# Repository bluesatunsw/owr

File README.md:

# owr
This repo includes all software necessary to operate the Test Rover Platform
that is being designed and developed in the OWR project.
=======

## System Setup
A guide is available on the
[owr-docs](https://github.com/bluesatunsw/owr-docs/tree/main/src/guides/container_setup.md)
repository.

## Useful Command index
| Command                                                               | Effect                                                                                          |
| -------------------------------                                       | --------------------------------                                                                |
| `podman compose -f "$PWD/.devcontainer/docker-compose.yml" up -d`     | Run in the git root to build/restart/start the Docker container.                                |
| `podman compose -f "$PWD/.devcontainer/docker-compose-obc.yml" up -d` | Run in the git root to build/restart/start the Docker container **with obc specific settings!** |
| `podman exec -it --latest /bin/bash`                                  | Enter the docker container after launching it with the devcontainer.                            |
| `./utils/init.bash`                                                   | Run after `cd`'ing into `/workspaces/owr` in the container to source the ROS env and tools      |
| `colcon build --symlink-install`                                      | Runs the `colcon` meta build system, builds ALL rover packages!                                 |
| `ros2 launch rover rover.launch.py`                                   | Launch the robot state publisher. Just leave this running.                                      |
| `rqt`                                                                 | The flexible ROS2 viewer, useful for debugging topic flows and looking at raw topics.           |
| `rviz2`                                                               | Useful for visualizing TF2 / LiDAR / etc... data to see if it looks okay.                       |
| `podman rm --force --latest -t 0`                                     | Kill the podman container with the latest creation date (quickly)                               |

NOTE: `podman compose` will take a VERY long time! on uni Wi-Fi \~5min due to
the amount of packages it installs (\~5GB). There is also [a podman
bug](github.com/containers/podman/issues/16541) that invokes a postprocessing
step on the overlay filesystem, this will take **upwards of 10 minutes!** 

NOTE: `./utils/init.bash` will source the appropriate files as well as put you
in a 10-deep nested shell - running an invalid command will kill 1 level!

### Less Common Commands

| Command                                                               | Effect                                                                                    |
| -------------------------------                                       | --------------------------------                                                          |
| `ros2 launch rover rsp.launch.py`                                     | Robot State Publisher, publishes the URDF+JSP, to make it viewable in Lichtblick / Rviz2. |
| `xacro ./src/rover/description/robot.urdf.xacro > ./build/rover.urdf` | Compiles the xacro into a singular urdf file                                              |
| `ros2 run key_teleop key_teleop --ros-args -p twist_stamped_enabled:=True -r /key_vel:=/diff_drive_base_controller/cmd_vel` | Record keyboard imputs and publish them as Twist2d values, which ROS2Control is listening for!

### Useful Podman Commands
| Command                                                               | Effect                                                                                    |
| -------------------------------                                       | ---------------------------------                                                         |
| `podman images`                                                       | Lists current podman images                                                               |
| `podman rmi {ID} --force`                                             | Remove relevant image. Replace the ID with output from the above command                  |

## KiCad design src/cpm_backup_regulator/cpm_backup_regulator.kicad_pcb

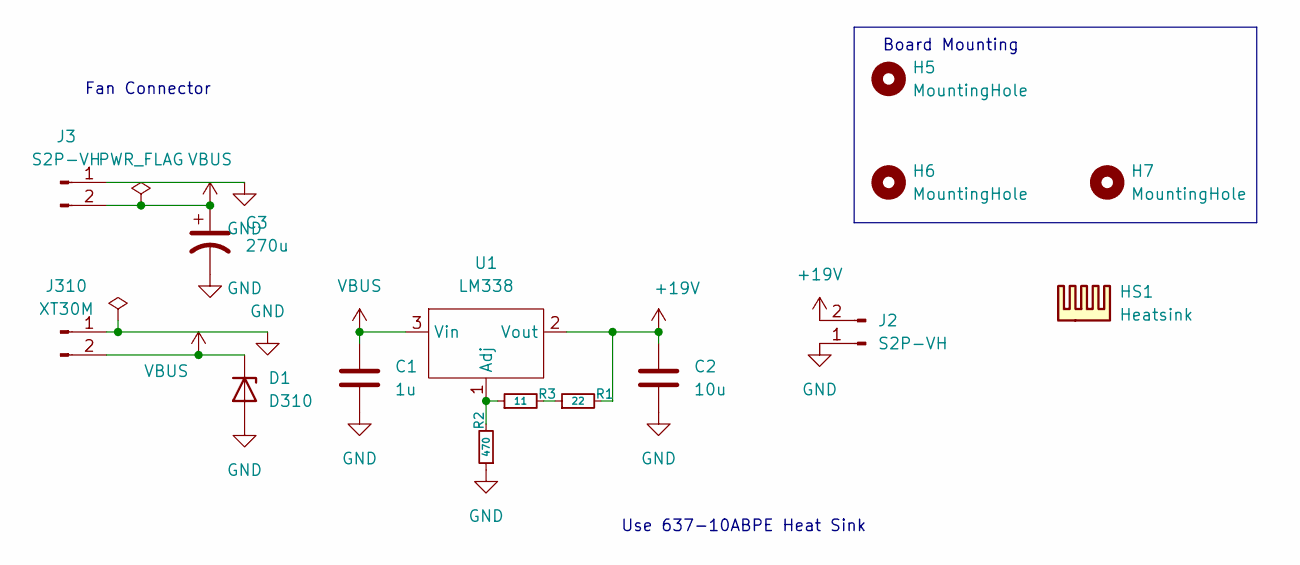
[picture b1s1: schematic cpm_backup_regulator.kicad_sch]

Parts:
C1: 1u; C_0805_2012Metric
C2: 10u; C_1210_3225Metric
C3: 270u; CP_Elec_10x10
D1: D310; D_SMF
H5, H6, H7: MountingHole; M2.5_Internal
HS1: Heatsink; Heatsink_Fischer_SK129-STS_42x25mm_2xDrill2.5mm
J2: S2P-VH; B2P-VH
J3: S2P-VH; BM02B-PASS
J310: XT30M; AMASS_XT30PW-M_1x02_P2.50mm_Horizontal
R1: 22; C_0402_1005Metric
R2: 470; C_0402_1005Metric
R3: 11; C_0402_1005Metric
U1: LM338; TO-220F-3_Vertical

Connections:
+19V: C2.1, J2.2, R1.2, U1.2 (Vout)
GND: C1.2, C2.2, C3.2, D1.2 (A), J2.1, J3.1, J310.1, R2.1
unnamed: R1.1, R3.2
unnamed: R2.2, R3.1, U1.1 (Adj)
VBUS: C1.1, C3.1, D1.1 (K), J3.2, J310.2, U1.3 (Vin)

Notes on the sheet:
Fan Connector
Board Mounting
Use 637-10ABPE Heat Sink

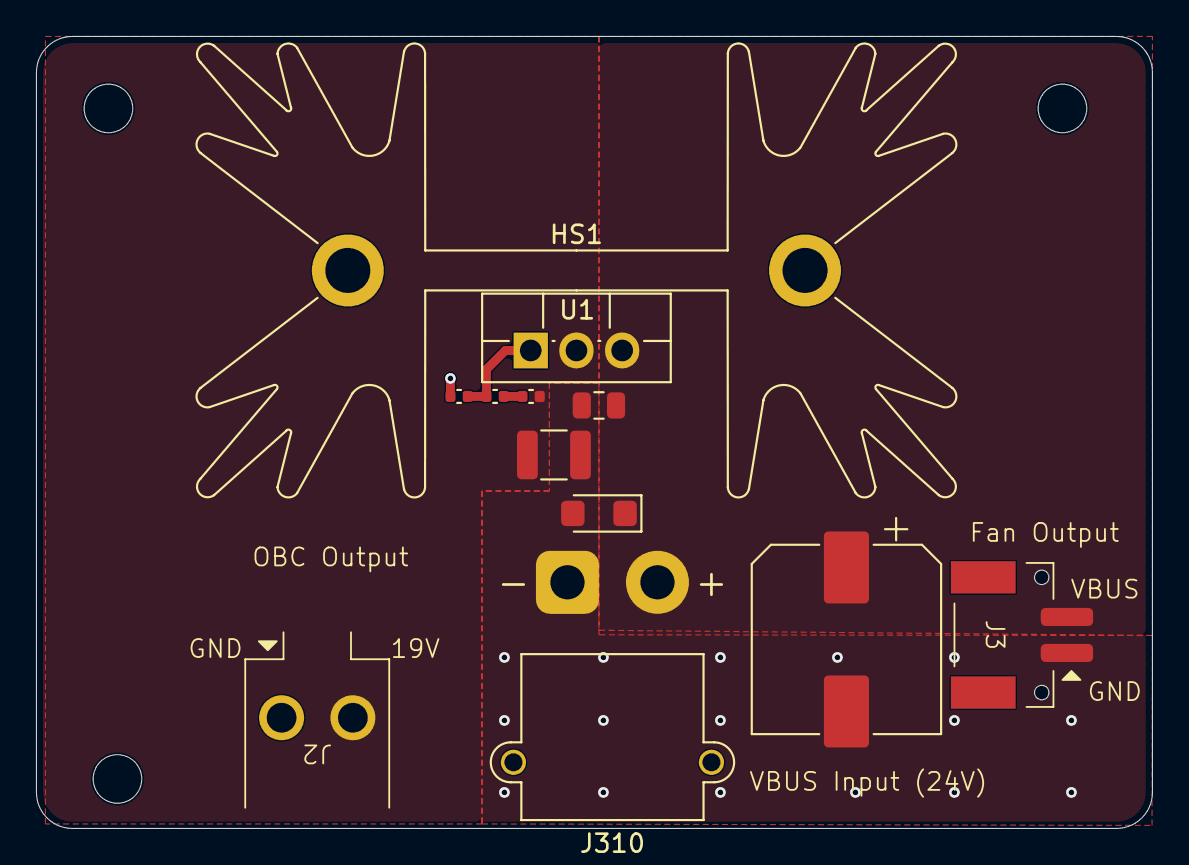
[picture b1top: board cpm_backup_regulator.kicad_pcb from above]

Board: 2 copper layers, 62.0 x 44.0 mm, 15 parts (0 on the bottom side), 5 nets.

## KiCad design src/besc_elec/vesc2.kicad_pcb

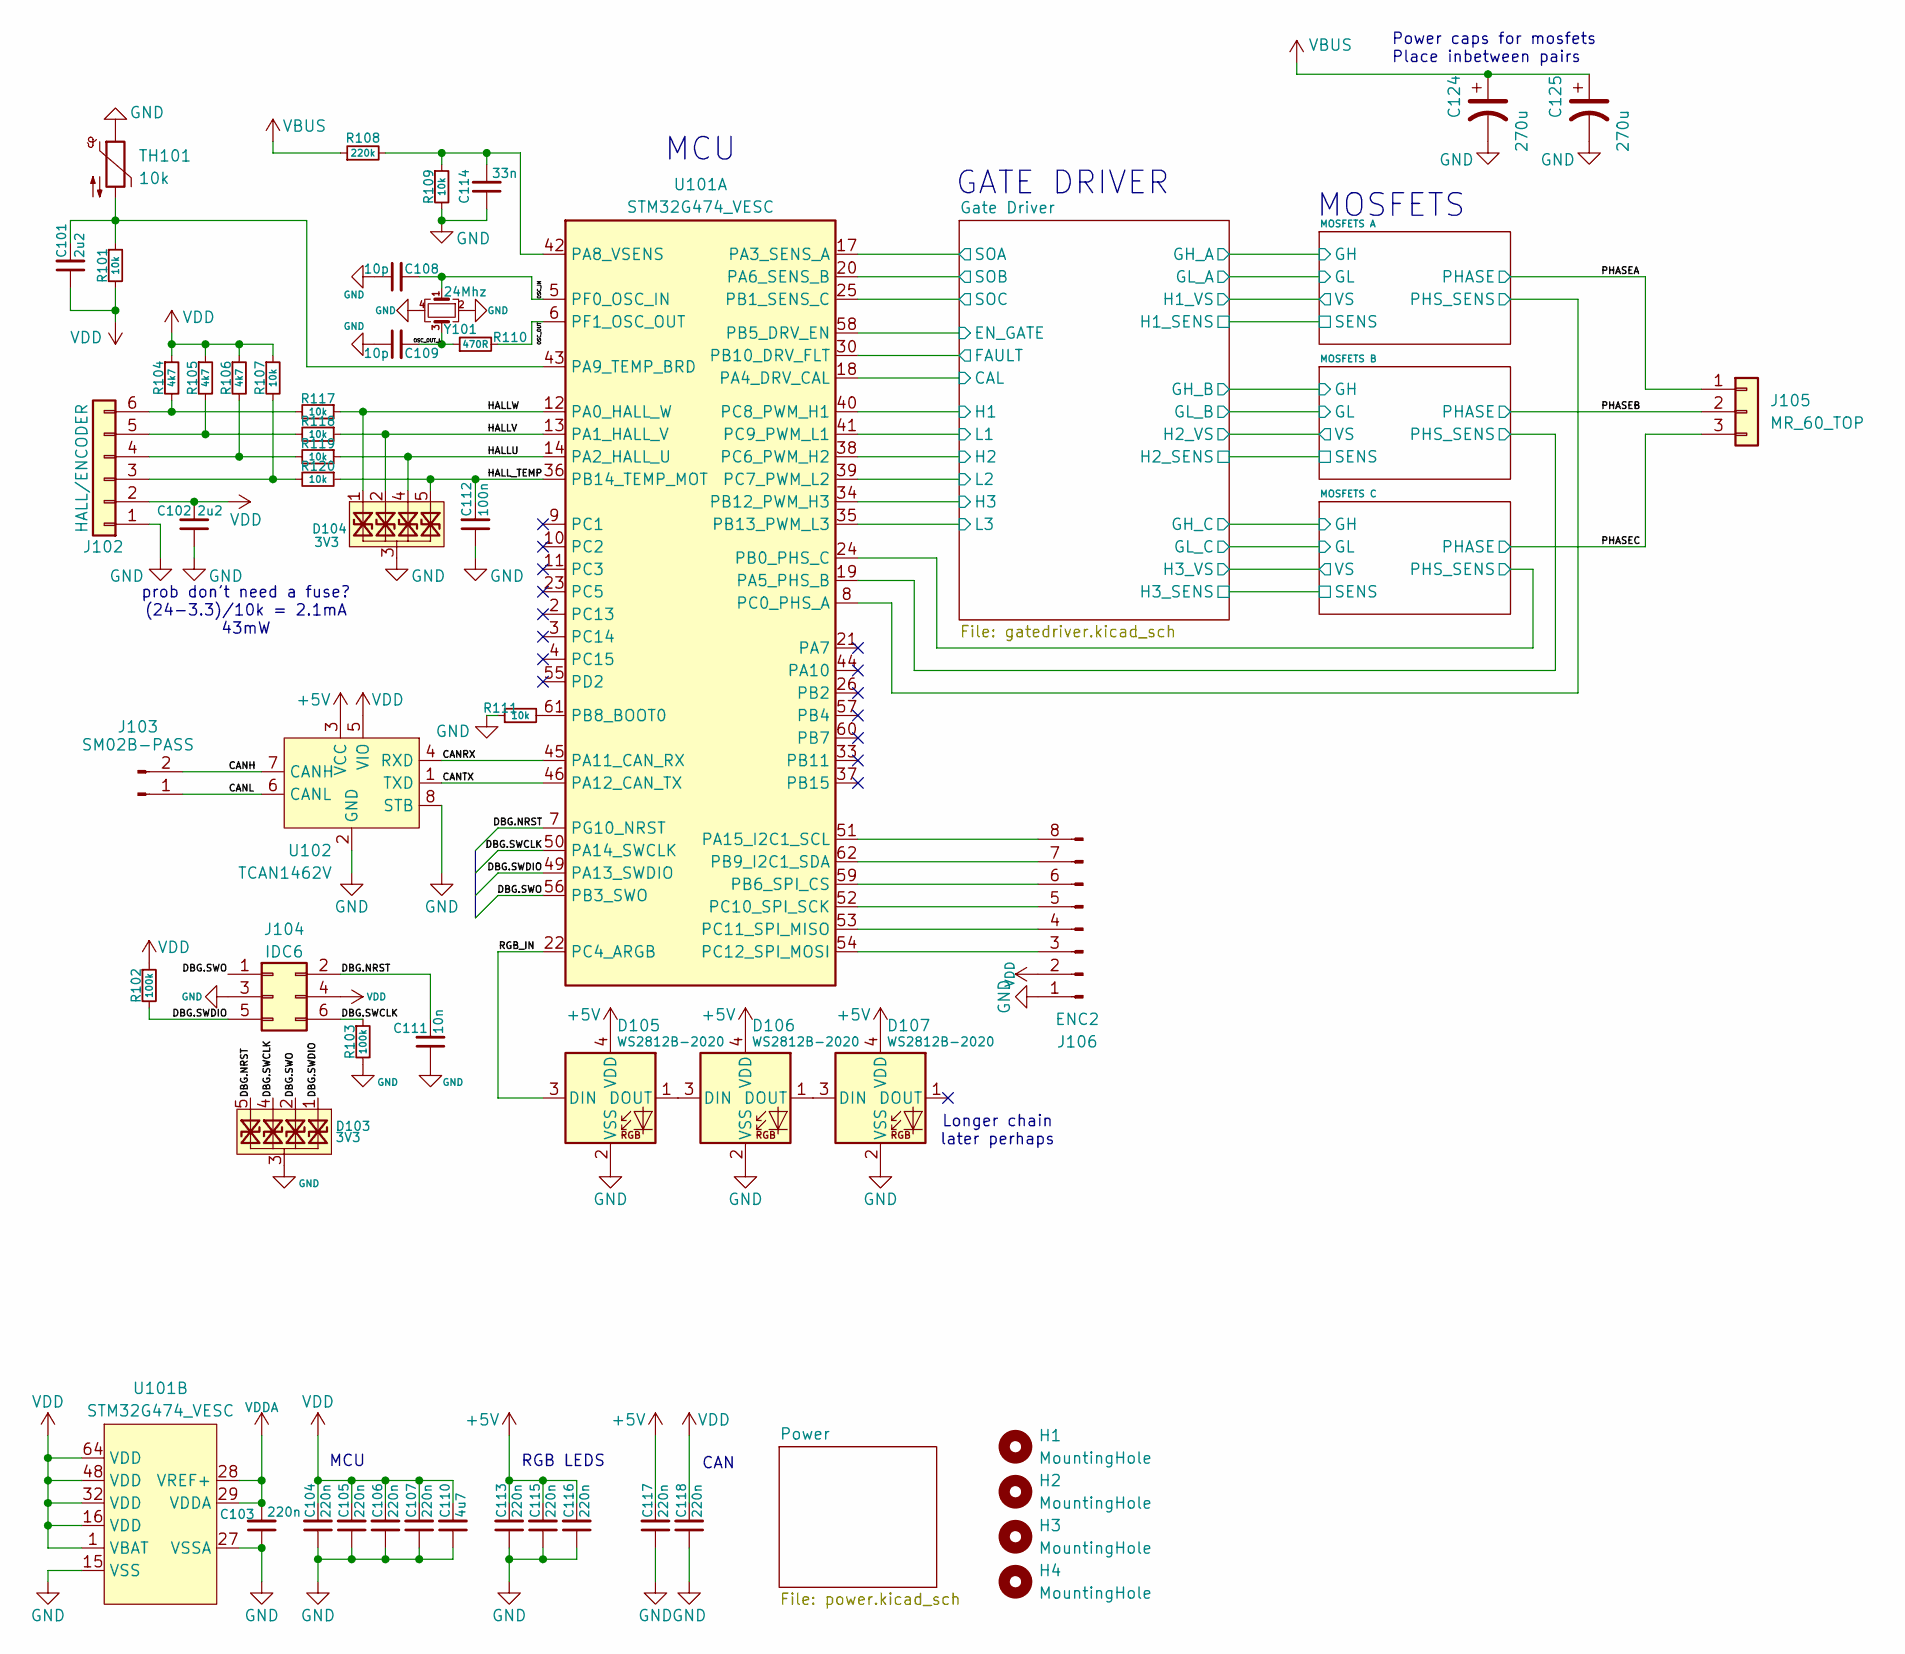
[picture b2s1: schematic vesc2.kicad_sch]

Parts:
C101, C102: 2u2; C_0603_1608Metric
C103, C104, C105, C106, C107, C113, C115, C116, C117, C118: 220n; C_0402_1005Metric
C108, C109: 10p; C_0402_1005Metric
C110: 4u7; C_0805_2012Metric
C111: 10n; C_0402_1005Metric
C112: 100n; C_0402_1005Metric
C114: 33n; C_0402_1005Metric
C124, C125: 270u; CP_Elec_10x10
D103, D104: 3V3; Diodes_UDFN-10_1x2.5mm_P0.5mm
D105, D106, D107: WS2812B-2020
H1, H2, H3, H4: MountingHole; M2.5_Edge
J102: HALL/ENCODER; BM06B-PASS
J103: SM02B-PASS; BM02B-PASS
J104: IDC6
J105: MR_60_TOP; MR60-F-TopMount
J106: ENC2; JST_PH_B8B-PH-SM4-TB_1x08-1MP_P2.00mm_Vertical
R101, R107, R109, R111, R117, R118, R119, R120: 10k; R_0402_1005Metric
R102, R103: 100k; R_0402_1005Metric
R104, R105, R106: 4k7; R_0402_1005Metric
R108: 220k; R_0402_1005Metric
R110: 470R; R_0402_1005Metric
TH101: 10k; R_0402_1005Metric
U101: STM32G474_VESC; LQFP-64-0.5
U102: TCAN1462V; SOIC-8_3.9x4.9mm_P1.27mm
Y101: 24Mhz; Crystal_SMD_2016-4Pin_2.0x1.6mm

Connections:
+5V: C113.2, C115.2, C116.2, C117.2, D105.4 (VDD), D106.4 (VDD), D107.4 (VDD), U102.3 (VCC); also elsewhere on the board
/CANH: J103.2, U102.7 (CANH)
/CANL: J103.1, U102.6 (CANL)
/CANRX: U101.45 (PA11_CAN_RX), U102.4 (RXD)
/CANTX: U101.46 (PA12_CAN_TX), U102.1 (TXD)
/DBG.NRST: C111.2, D103.5, D103.6, J104.2, U101.7 (PG10_NRST)
/DBG.SWCLK: D103.4, D103.7, J104.6, R103.1, U101.50 (PA14_SWCLK)
/DBG.SWDIO: D103.1, D103.10, J104.5, R102.2, U101.49 (PA13_SWDIO)
/DBG.SWO: D103.2, D103.9, J104.1, U101.56 (PB3_SWO)
/Gate Driver/CAL: U101.18 (PA4_DRV_CAL); also elsewhere on the board
/Gate Driver/EN_GATE: U101.58 (PB5_DRV_EN); also elsewhere on the board
/Gate Driver/FAULT: U101.30 (PB10_DRV_FLT); also elsewhere on the board
/Gate Driver/H1: U101.40 (PC8_PWM_H1); also elsewhere on the board
/Gate Driver/H2: U101.38 (PC6_PWM_H2); also elsewhere on the board
/Gate Driver/H3: U101.34 (PB12_PWM_H3); also elsewhere on the board
/Gate Driver/L1: U101.41 (PC9_PWM_L1); also elsewhere on the board
/Gate Driver/L2: U101.39 (PC7_PWM_L2); also elsewhere on the board
/Gate Driver/L3: U101.35 (PB13_PWM_L3); also elsewhere on the board
/Gate Driver/SOA: U101.17 (PA3_SENS_A); also elsewhere on the board
/Gate Driver/SOB: U101.20 (PA6_SENS_B); also elsewhere on the board
/Gate Driver/SOC: U101.25 (PB1_SENS_C); also elsewhere on the board
/HALLU: D104.4, D104.7, R119.1, U101.14 (PA2_HALL_U)
/HALLV: D104.2, D104.9, R118.1, U101.13 (PA1_HALL_V)
/HALLW: D104.1, D104.10, R117.1, U101.12 (PA0_HALL_W)
/HALL_TEMP: C112.2, D104.5, D104.6, R120.1, U101.36 (PB14_TEMP_MOT)
/MOSFETS A/PHS_SENS: U101.8 (PC0_PHS_A); also elsewhere on the board
/MOSFETS B/PHS_SENS: U101.19 (PA5_PHS_B); also elsewhere on the board
/MOSFETS C/PHS_SENS: U101.24 (PB0_PHS_C); also elsewhere on the board
/OSC_IN: C108.2, U101.5 (PF0_OSC_IN), Y101.1
/OSC_OUT: R110.2, U101.6 (PF1_OSC_OUT)
/OSC_OUT_L: C109.2, R110.1, Y101.3
/PHASEA: J105.1; also elsewhere on the board
/PHASEB: J105.2; also elsewhere on the board
/PHASEC: J105.3; also elsewhere on the board
/RGB_IN: D105.3 (DIN), U101.22 (PC4_ARGB)
GND: C102.1, C103.1, C104.1, C105.1, C106.1, C107.1, C108.1, C109.1, C110.1, C111.1, C112.1, C113.1, C114.1, C115.1, C116.1, C117.1, C118.1, C124.2, C125.2, D103.3, D103.8, D104.3, D104.8, D105.2 (VSS), D106.2 (VSS), D107.2 (VSS), J102.1, J104.3, J106.1, R103.2, R109.2, R111.1, TH101.1, U101.15 (VSS), U101.27 (VSSA), U101.31 (VSS), U101.47 (VSS), U101.63 (VSS), U102.2 (GND), U102.8 (STB), Y101.2, Y101.4; also elsewhere on the board
unnamed: D105.1 (DOUT), D106.3 (DIN)
unnamed: D106.1 (DOUT), D107.3 (DIN)
unnamed: J102.3, R107.2, R120.2
unnamed: J102.4, R106.2, R119.2
unnamed: J102.5, R105.2, R118.2
unnamed: J102.6, R104.2, R117.2
unnamed: J106.3, U101.54 (PC12_SPI_MOSI)
unnamed: J106.4, U101.53 (PC11_SPI_MISO)
unnamed: J106.5, U101.52 (PC10_SPI_SCK)
unnamed: J106.6, U101.59 (PB6_SPI_CS)
unnamed: J106.7, U101.62 (PB9_I2C1_SDA)
unnamed: J106.8, U101.51 (PA15_I2C1_SCL)
unnamed: C114.2, R108.2, R109.1, U101.42 (PA8_VSENS)
unnamed: C101.2, R101.1, TH101.2, U101.43 (PA9_TEMP_BRD)
unnamed: R111.2, U101.61 (PB8_BOOT0)
VBUS: C124.1, C125.1, R108.1; also elsewhere on the board
VDD: C101.1, C102.2, C104.2, C105.2, C106.2, C107.2, C110.2, C118.2, J102.2, J104.4, J106.2, R101.2, R102.1, R104.1, R105.1, R106.1, R107.1, U101.1 (VBAT), U101.16 (VDD), U101.32 (VDD), U101.48 (VDD), U101.64 (VDD), U102.5 (VIO); also elsewhere on the board
VDDA: C103.2, U101.28 (VREF+), U101.29 (VDDA); also elsewhere on the board

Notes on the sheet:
RGB LEDS
Power caps for mosfets Place inbetween pairs
GATE DRIVER
MCU
CAN
MOSFETS
prob don't need a fuse? (24-3.3)/10k = 2.1mA 43mW
Longer chain later perhaps

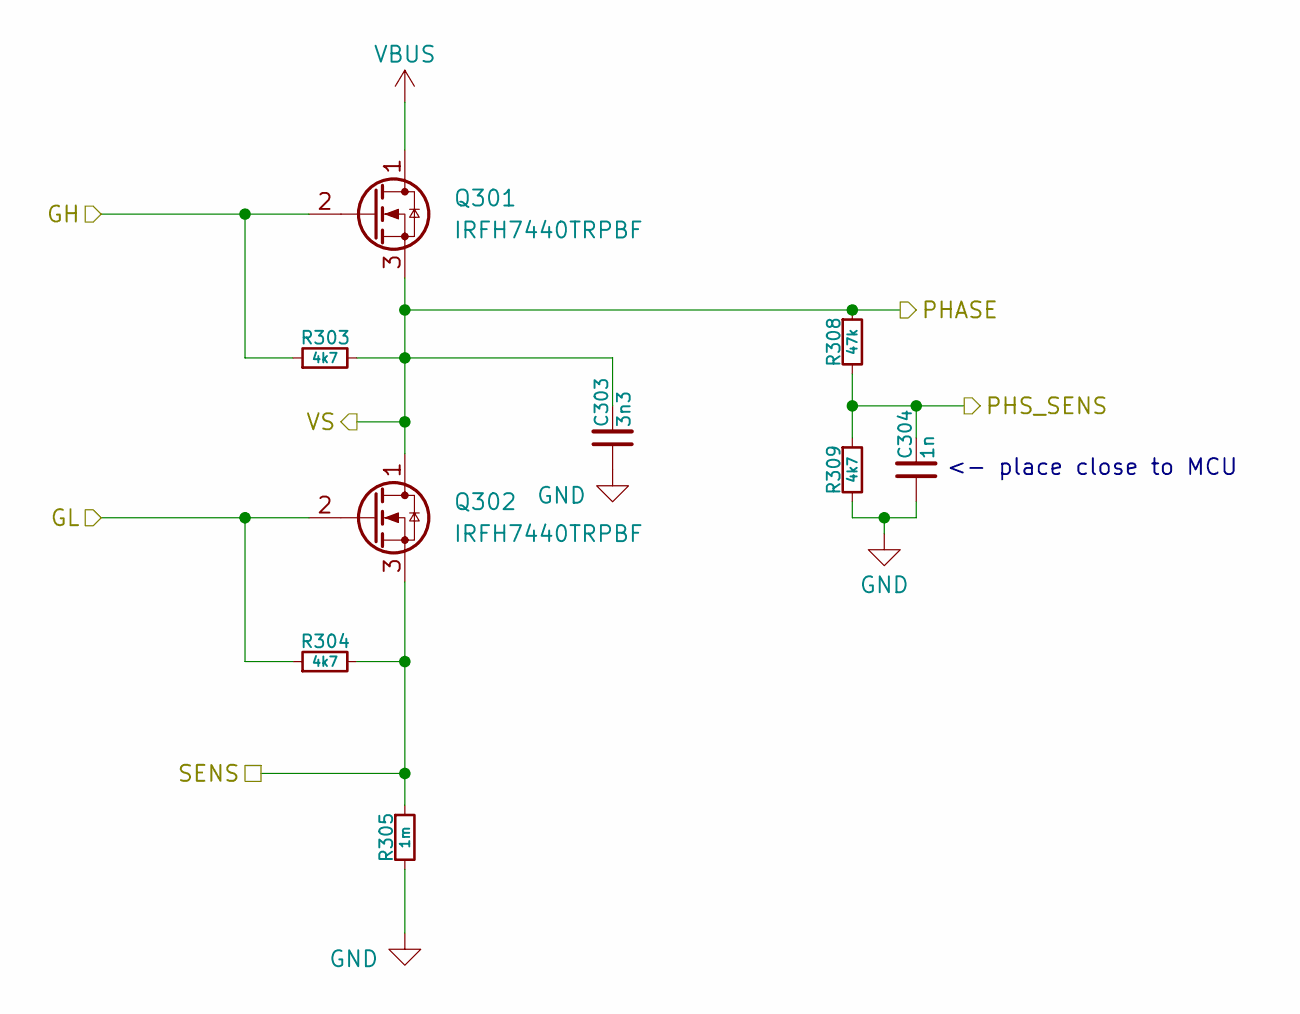
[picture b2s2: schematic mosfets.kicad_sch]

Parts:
C303: 3n3; C_0402_1005Metric
C304: 1n; C_0402_1005Metric
Q301, Q302: IRFH7440TRPBF; PQFN_5x6mm_E_DGS
R303, R304, R309: 4k7; R_0402_1005Metric
R305: 1m; R_2512_6332Metric
R308: 47k; R_0402_1005Metric

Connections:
/Gate Driver/GH_A: Q301.2 (G), R303.1; also elsewhere on the board
/Gate Driver/GL_A: Q302.2 (G), R304.1; also elsewhere on the board
/Gate Driver/H1_SENS: Q302.3 (S), R304.2, R305.1; also elsewhere on the board
/MOSFETS A/PHS_SENS: C304.2, R308.2, R309.1; also elsewhere on the board
/PHASEA: C303.2, Q301.3 (S), Q302.1 (D), R303.2, R308.1; also elsewhere on the board
GND: C303.1, C304.1, R305.2, R309.2; also elsewhere on the board
VBUS: Q301.1 (D); also elsewhere on the board

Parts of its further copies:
C403, C503: 3n3; C_0402_1005Metric
C404, C504: 1n; C_0402_1005Metric
Q401, Q402, Q501, Q502: IRFH7440TRPBF; PQFN_5x6mm_E_DGS
R403, R404, R408, R503, R504, R508: 4k7; R_0402_1005Metric
R405, R505: 1m; R_2512_6332Metric
R409, R509: 47k; R_0402_1005Metric

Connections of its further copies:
/Gate Driver/GH_B: Q401.2 (G), R403.1; also elsewhere on the board
/Gate Driver/GH_C: Q501.2 (G), R503.1; also elsewhere on the board
/Gate Driver/GL_B: Q402.2 (G), R404.1; also elsewhere on the board
/Gate Driver/GL_C: Q502.2 (G), R504.1; also elsewhere on the board
/Gate Driver/H2_SENS: Q402.3 (S), R404.2, R405.1; also elsewhere on the board
/Gate Driver/H3_SENS: Q502.3 (S), R504.2, R505.1; also elsewhere on the board
/MOSFETS B/PHS_SENS: C404.2, R408.1, R409.2; also elsewhere on the board
/MOSFETS C/PHS_SENS: C504.2, R508.1, R509.2; also elsewhere on the board
/PHASEB: C403.2, Q401.3 (S), Q402.1 (D), R403.2, R409.1; also elsewhere on the board
/PHASEC: C503.2, Q501.3 (S), Q502.1 (D), R503.2, R509.1; also elsewhere on the board
GND: C403.1, C404.1, C503.1, C504.1, R405.2, R408.2, R505.2, R508.2; also elsewhere on the board
VBUS: Q401.1 (D), Q501.1 (D); also elsewhere on the board

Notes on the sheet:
<- place close to MCU

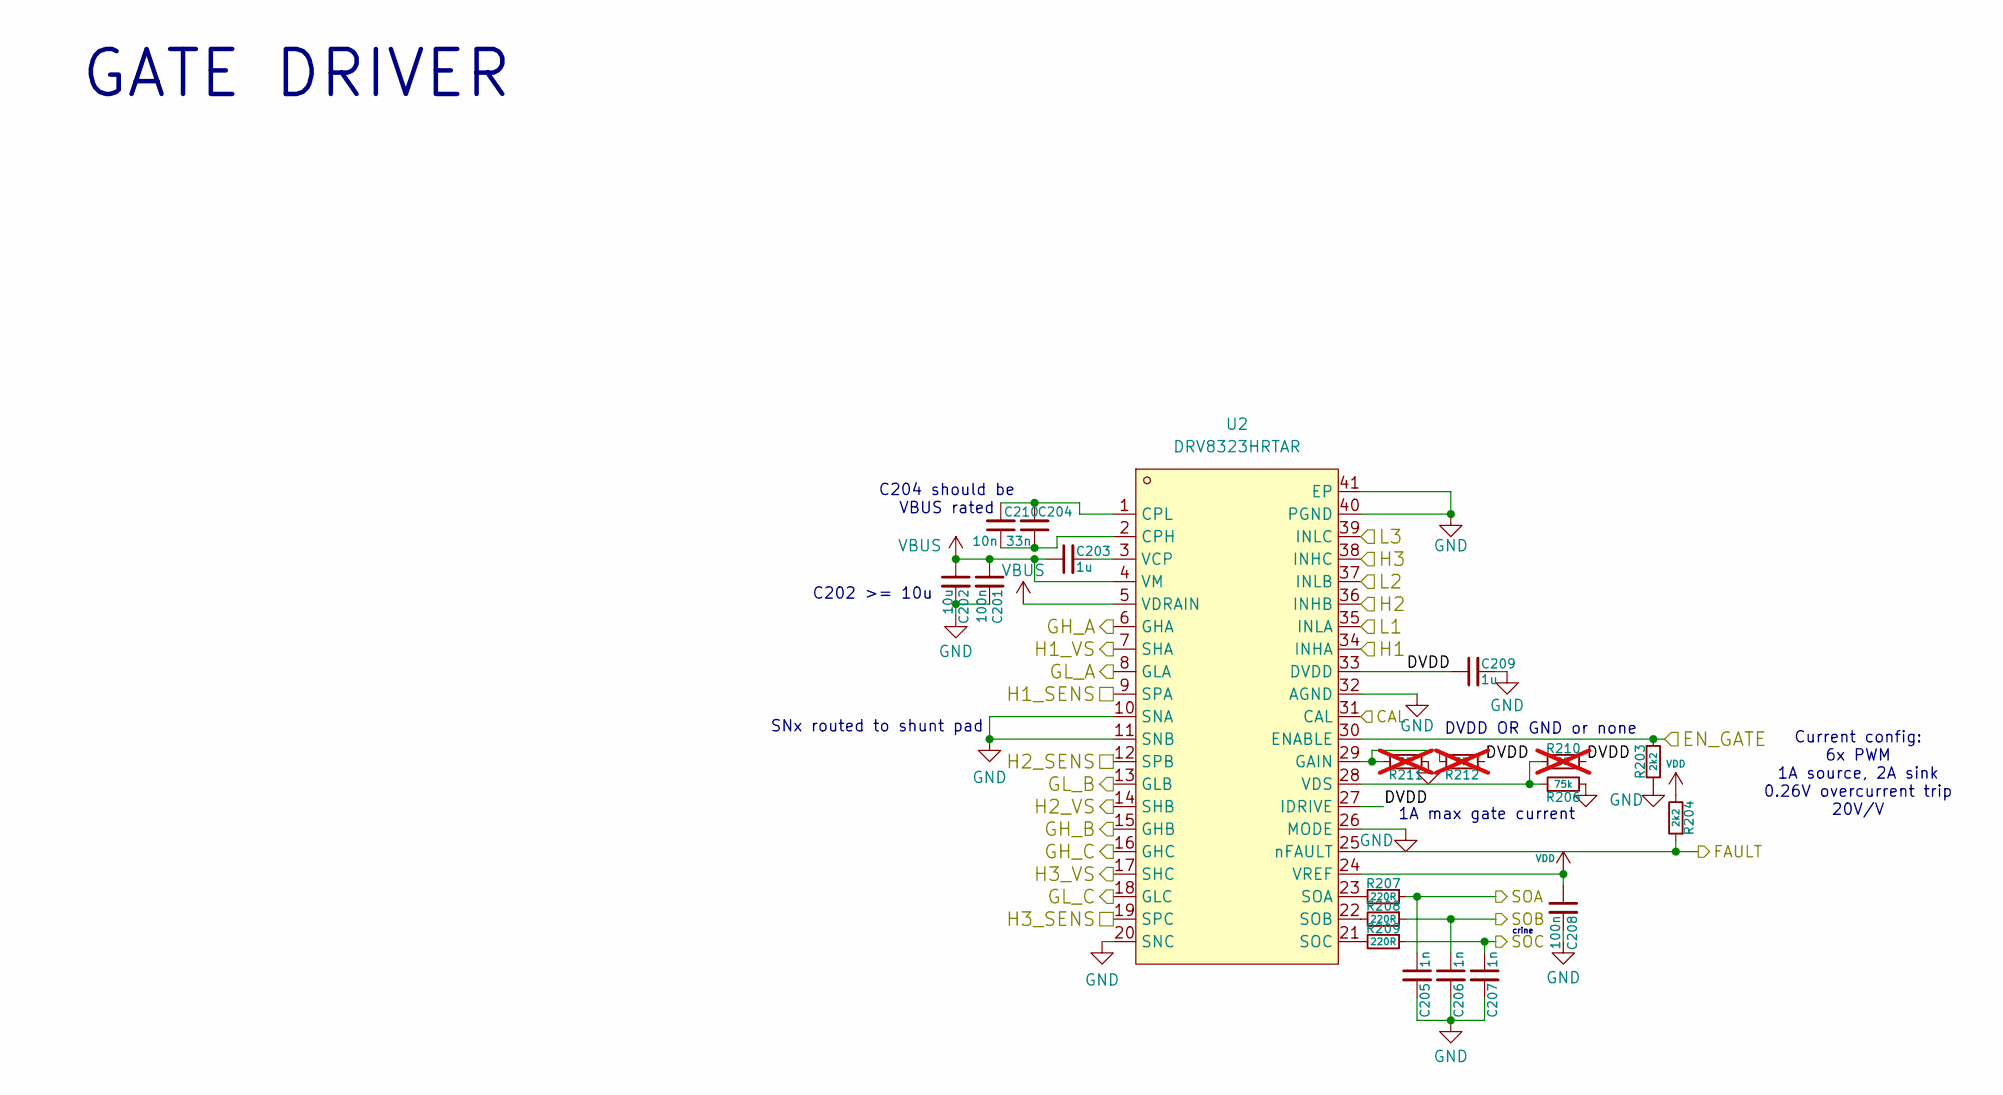
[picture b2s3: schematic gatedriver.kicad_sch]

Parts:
C201: 100n; C_0603_1608Metric
C202: 10u; C_1210_3225Metric
C203: 1u; C_0805_2012Metric
C204: 33n; C_0603_1608Metric
C205, C206, C207: 1n; C_0402_1005Metric
C208: 100n; C_0402_1005Metric
C209: 1u; C_0603_1608Metric
C210: 10n; C_0603_1608Metric
R203, R204: 2k2; R_0402_1005Metric
R206: 75k; R_0402_1005Metric
R207, R208, R209: 220R; R_0402_1005Metric
R210, R211, R212: 0R; R_0402_1005Metric; not fitted
U2: DRV8323HRTAR; QFN-40_L6.0-W6.0-P0.50-BL-EP4.5; MPN DRV8323HRTAR; LCSC Part C701783

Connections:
/Gate Driver/CAL: U2.31 (CAL); also elsewhere on the board
/Gate Driver/DVDD: C209.1, R210.1, R212.2, U2.27 (IDRIVE), U2.33 (DVDD)
/Gate Driver/EN_GATE: R203.1, U2.30 (ENABLE); also elsewhere on the board
/Gate Driver/FAULT: R204.1, U2.25 (nFAULT); also elsewhere on the board
/Gate Driver/GH_A: U2.6 (GHA); also elsewhere on the board
/Gate Driver/GH_B: U2.15 (GHB); also elsewhere on the board
/Gate Driver/GH_C: U2.16 (GHC); also elsewhere on the board
/Gate Driver/GL_A: U2.8 (GLA); also elsewhere on the board
/Gate Driver/GL_B: U2.13 (GLB); also elsewhere on the board
/Gate Driver/GL_C: U2.18 (GLC); also elsewhere on the board
/Gate Driver/H1: U2.34 (INHA); also elsewhere on the board
/Gate Driver/H1_SENS: U2.9 (SPA); also elsewhere on the board
/Gate Driver/H2: U2.36 (INHB); also elsewhere on the board
/Gate Driver/H2_SENS: U2.12 (SPB); also elsewhere on the board
/Gate Driver/H3: U2.38 (INHC); also elsewhere on the board
/Gate Driver/H3_SENS: U2.19 (SPC); also elsewhere on the board
/Gate Driver/L1: U2.35 (INLA); also elsewhere on the board
/Gate Driver/L2: U2.37 (INLB); also elsewhere on the board
/Gate Driver/L3: U2.39 (INLC); also elsewhere on the board
/Gate Driver/SOA: C205.1, R207.1; also elsewhere on the board
/Gate Driver/SOB: C206.1, R208.1; also elsewhere on the board
/Gate Driver/SOC: C207.1, R209.1; also elsewhere on the board
/PHASEA: U2.7 (SHA); also elsewhere on the board
/PHASEB: U2.14 (SHB); also elsewhere on the board
/PHASEC: U2.17 (SHC); also elsewhere on the board
GND: C201.2, C202.2, C205.2, C206.2, C207.2, C208.2, C209.2, R203.2, R206.2, R211.2, U2.10 (SNA), U2.11 (SNB), U2.20 (SNC), U2.26 (MODE), U2.32 (AGND), U2.40 (PGND), U2.41 (EP); also elsewhere on the board
unnamed: C204.1, C210.1, U2.2 (CPH)
unnamed: C204.2, C210.2, U2.1 (CPL)
unnamed: R211.1, R212.1, U2.29 (GAIN)
unnamed: R207.2, U2.23 (SOA)
unnamed: R208.2, U2.22 (SOB)
unnamed: R209.2, U2.21 (SOC)
unnamed: C203.2, U2.3 (VCP)
unnamed: R206.1, R210.2, U2.28 (VDS)
VBUS: C201.1, C202.1, C203.1, U2.4 (VM), U2.5 (VDRAIN); also elsewhere on the board
VDD: C208.1, R204.2, U2.24 (VREF); also elsewhere on the board

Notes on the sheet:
C204 should be VBUS rated
GATE DRIVER
Current config: 6x PWM 1A source, 2A sink 0.26V overcurrent trip 20V/V
DVDD OR GND or none
SNx routed to shunt pad
C202 >= 10u
crine
1A max gate current

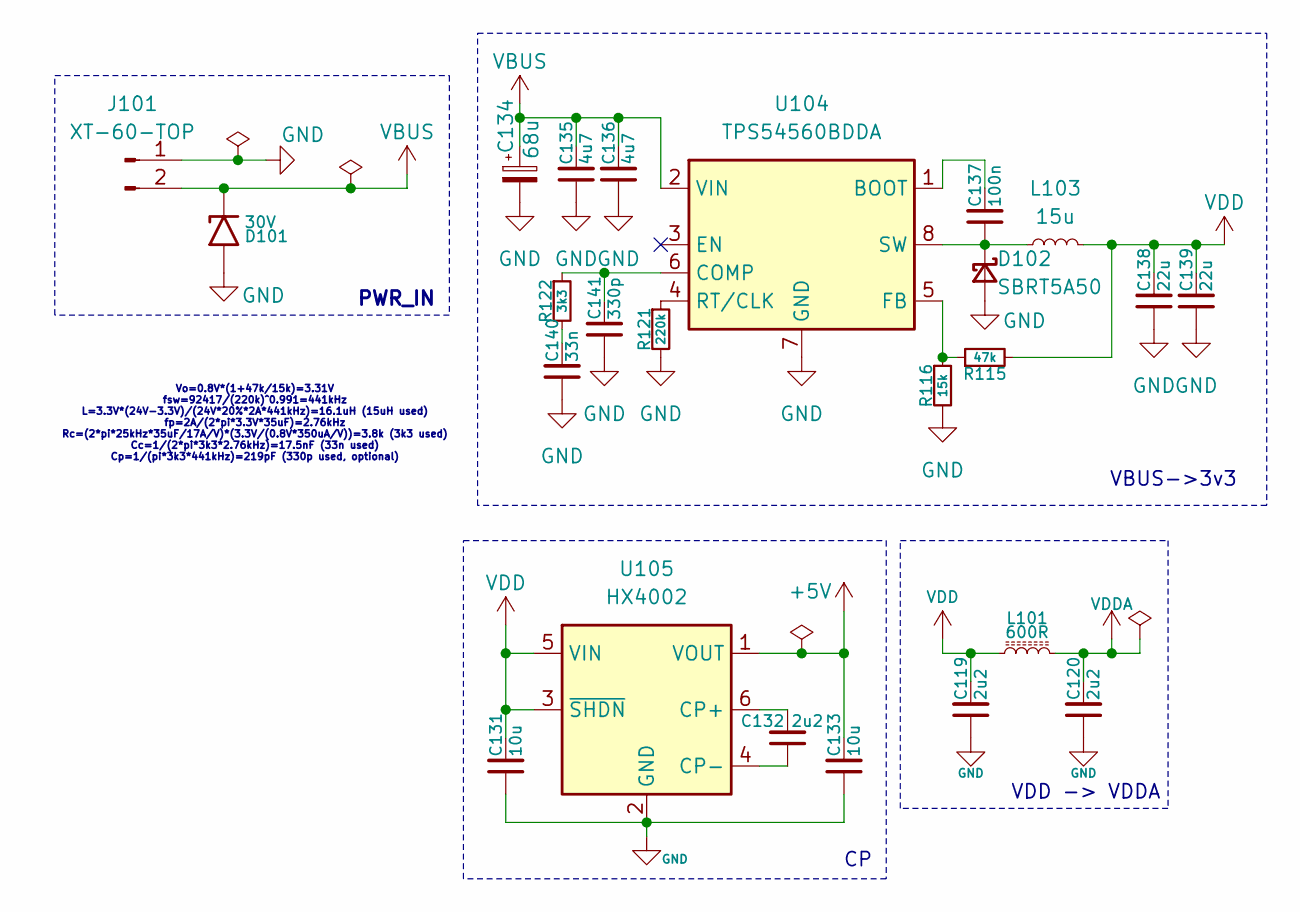
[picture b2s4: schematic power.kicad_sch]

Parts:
C119, C120, C132: 2u2; C_0603_1608Metric
C131, C133: 10u; C_1206_3216Metric
C134: 68u; CP_Elec_6.3x7.7
C135, C136: 4u7; C_1210_3225Metric
C137: 100n; C_0402_1005Metric
C138, C139: 22u; C_1210_3225Metric
C140: 33n; C_0402_1005Metric
C141: 330p; C_0402_1005Metric
D101: 30V; D_SMF
D102: SBRT5A50; D_SMA
J101: XT-60-TOP; AMASS_XT60-M_1x02_P7.20mm_Vertical
L101: 600R; R_0402_1005Metric
L103: 15u; L_Changjiang_FNR5040S
R115: 47k; R_0402_1005Metric
R116: 15k; R_0402_1005Metric
R121: 220k; R_0402_1005Metric
R122: 3k3; R_0402_1005Metric
U104: TPS54560BDDA; Texas_R-PDSO-G8_EP2.95x4.9mm_Mask2.4x3.1mm_ThermalVias
U105: HX4002; SOT-23-6

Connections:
+5V: C133.2, U105.1 (VOUT); also elsewhere on the board
GND: C119.1, C120.1, C131.1, C133.1, C134.2, C135.1, C136.1, C138.1, C139.1, C140.1, C141.1, D101.2 (A2), D102.2 (A), J101.1, R116.2, R121.2, U104.7 (GND), U104.9 (GND), U105.2 (GND); also elsewhere on the board
unnamed: C140.2, R122.2
unnamed: C137.1, D102.1 (K), L103.1, U104.8 (SW)
unnamed: C137.2, U104.1 (BOOT)
unnamed: C141.2, R122.1, U104.6 (COMP)
unnamed: R115.1, R116.1, U104.5 (FB)
unnamed: R121.1, U104.4 (RT/CLK)
unnamed: C132.2, U105.6 (CP+)
unnamed: C132.1, U105.4 (CP-)
VBUS: C134.1, C135.2, C136.2, D101.1 (A1), J101.2, U104.2 (VIN); also elsewhere on the board
VDD: C119.2, C131.2, C138.2, C139.2, L101.1, L103.2, R115.2, U105.3 (~SHDN), U105.5 (VIN); also elsewhere on the board
VDDA: C120.2, L101.2; also elsewhere on the board

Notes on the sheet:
VDD -> VDDA
Vo=0.8V*(1+47k/15k)=3.31V fsw=92417/(220k)^0.991=441kHz L=3.3V*(24V-3.3V)/(24V*20%*2A*441kHz)=16.1uH (15uH used) fp=2A/(2*pi*3.3V*35uF)=2.76kHz Rc=(2*pi*25kHz*35uF/17A/V)*(3.3V/(0.8V*350uA/V))=3.8k (3k3 used) Cc=1/(2*pi*3k3*2.76kHz)=17.5nF (33n used) Cp=1/(pi*3k3*441kHz)=219pF (330p used, optional)
VBUS->3v3
PWR_IN

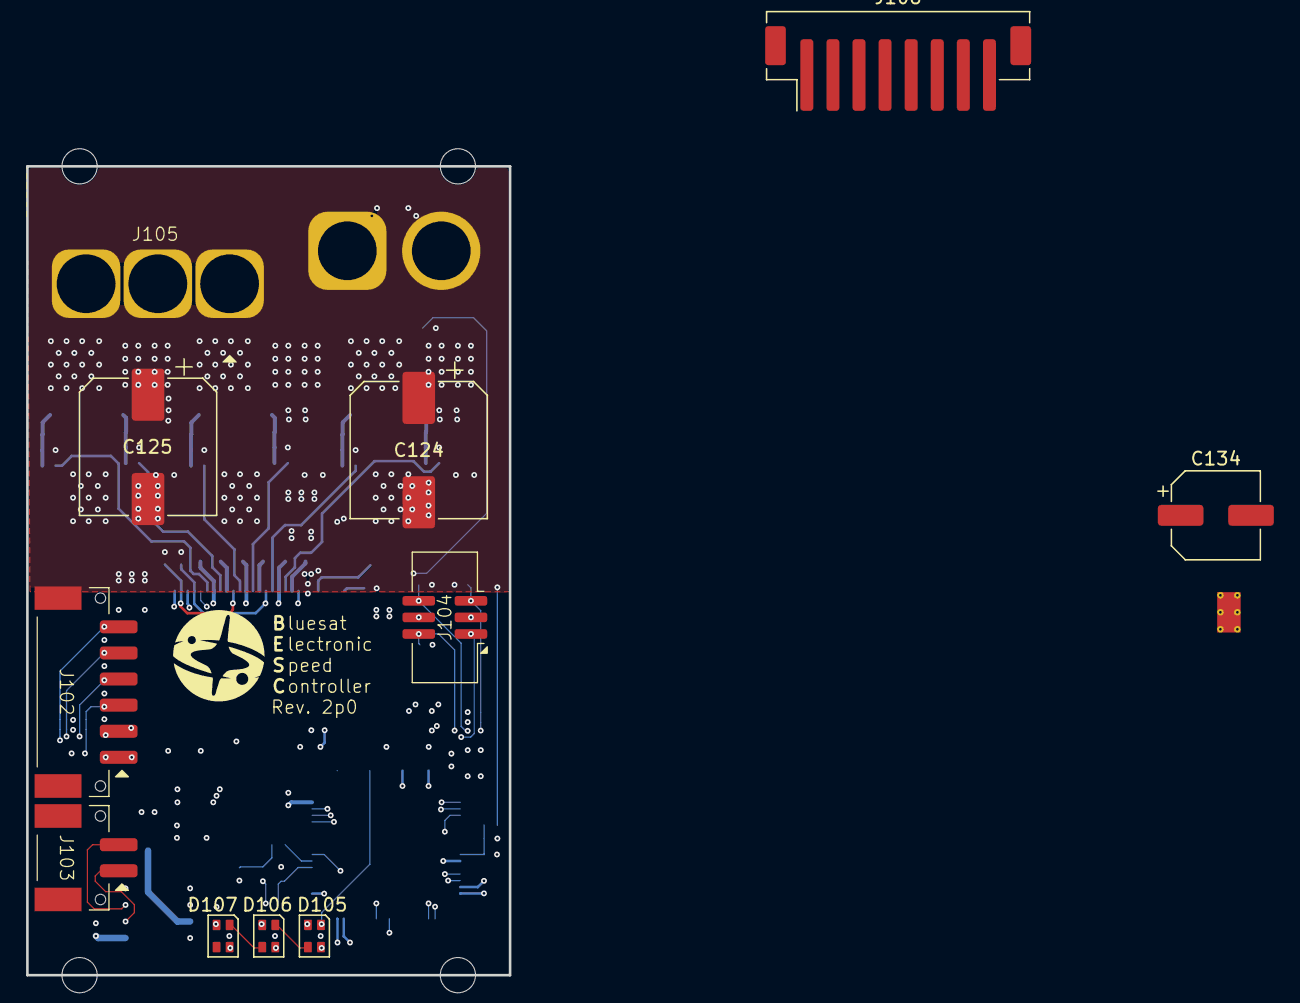
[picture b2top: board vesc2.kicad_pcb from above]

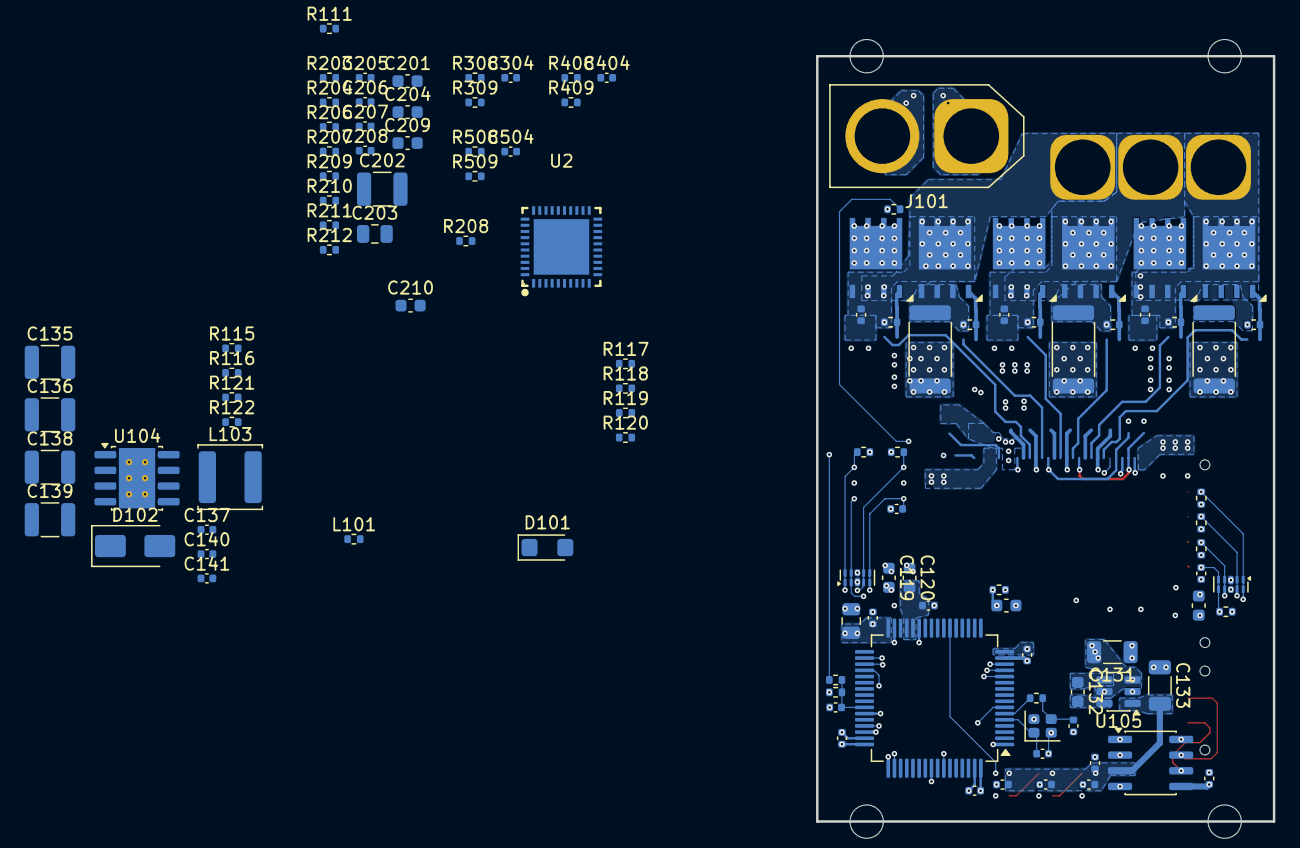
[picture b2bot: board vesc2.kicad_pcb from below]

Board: 6 copper layers, 37.0 x 62.0 mm, 124 parts (109 on the bottom side), 80 nets.

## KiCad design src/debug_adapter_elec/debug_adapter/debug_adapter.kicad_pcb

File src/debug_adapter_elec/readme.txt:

STLink V3 clone: https://www.alibaba.com/product-detail/Weact-STLink-DAP-Link-ARM-debugger_1601206848066.html
STLink V2 clone: https://www.alibaba.com/product-detail/ST-LINK-V2-STM8-STM32-simulator_1601017055060.html

Connector to V3: JST-SH 10 pin horizontal - https://www.lcsc.com/product-detail/C160409.html
Connector to V2: 2x5 vertical keyed duponts - https://www.lcsc.com/product-detail/C358740.html
Connector to device under test (DUT): standard IDC6 connector permanently connected using epoxy - https://www.lcsc.com/product-detail/C42372553.html

more info on the github issue: https://github.com/bluesatunsw/owr-docs/issues/446

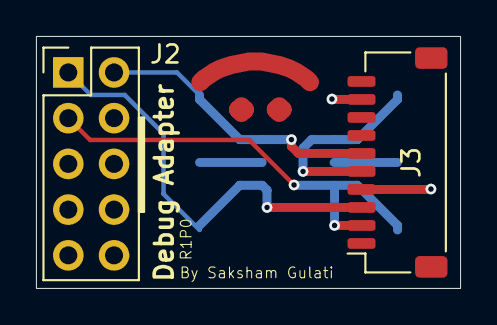
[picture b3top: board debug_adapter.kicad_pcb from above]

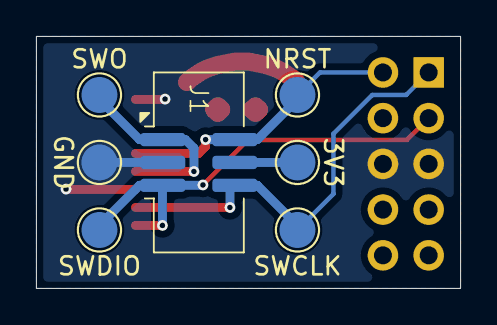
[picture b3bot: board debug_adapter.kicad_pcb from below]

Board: 2 copper layers, 23.6 x 14.0 mm, 9 parts (7 on the bottom side), 6 nets.

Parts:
3V3: TestPoint; TestPoint_Pad_D2.0mm
GND: TestPoint; TestPoint_Pad_D2.0mm
J1: Conn_02x03_Odd_Even; IDC6
J2: Conn_02x05_Odd_Even; PinHeader_2x05_P2.54mm_Vertical
J3: Conn_01x10; JST_SH_SM10B-SRSS-TB_1x10-1MP_P1.00mm_Horizontal
NRST: TestPoint; TestPoint_Pad_D2.0mm
SWCLK: TestPoint; TestPoint_Pad_D2.0mm
SWDIO: TestPoint; TestPoint_Pad_D2.0mm
SWO: TestPoint; TestPoint_Pad_D2.0mm

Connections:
/3V3: 3V3.1 (1_1), J1.4
/GND: GND.1 (1_1), J1.3, J2.5, J2.6, J3.4, J3.9
/NRST: J1.2, J2.2, J3.6, NRST.1 (1_1)
/SWCLK: J1.6, J2.1, J3.3, SWCLK.1 (1_1)
/SWDIO: J1.5, J2.3, J3.2, SWDIO.1 (1_1)
/SWO: J1.1, J3.5, SWO.1 (1_1)
